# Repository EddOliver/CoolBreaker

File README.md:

# CoolBreaker: Automotive Smart Circuit breaker, and switch

https://www.hackster.io/Edoliver/coolbreaker-automotive-smart-circuit-breaker-and-switch-d4b7d0

## Automotive Smart Circuit breaker and switch to increase efficiency in your car's electrical system and prevent electrical hazards.

## Bill of Materials

Hardware components
- CoolMOS C7 Gold SJ MOSFET	
- Infineon CoolMOS C7 Gold SJ MOSFET×	1	
- Custom PCB	
- Adafruit Feather HUZZAH with ESP32×	1	
- Infineon EiceDriver	x1	
- Capacitor 100 nF	
- Capacitor 10 µF
- 10R Resistor
- 3R3 Resistor	
- DFRobot ACS758 Current Sensor board

Software apps and online services
- Autodesk Eagle
- Fusion 360	
- Autodesk Fusion 360

## Story
CoolBreaker: Automotive Smart Circuit breaker, battery protection and switch.

## Introduction and problem
For several years now the automotive industry have relied on car fuses as they are cheap and easily changeable. Most cars have a fuse box that looks like this in order to manage their electrical system:

Even Teslas use a fuse box when dealing with Accesory wiring and internal electrical systems:

https://www.carcarekiosk.com/video/2017_Tesla_S_90D_Electric/fuse_interior/replace

Ordinary car fuses generally used in most applications have several drawbacks and they can be inefficient in case of a short circuit or with faulty electrical systems. If you don't believe me, let's ask motoforlife:

https://www.youtube.com/watch?v=sIqoVgxmnvQ

Nowadays we have cars with a lot of accesories. Lights, USB ports that in turn power more devices, audio systems, even refrigerators in some trucks and more. And we want even more stuff.

But, what do we have in hand for electrical automotive protection?

1.- More Fuses (with all their drawbacks).

2.- Mechanical and electromechanical Circuit breakers.

3.- Relay harnesses.

Lets analyze both options:

### Fuses and Relays

Relays are everywhere in a car, and they are seldom solid state ones.

Well, fuses are just like the ones we used to have at homes or in home appliances. As a current above their limit passes through the wire, it melts it breaking it and thus the circuit. There's a huge reason we have already moved on from those in relation to home use as they are unreliable and almost dangerous in some aspects. Yes, the automotive industry uses them because they are cheap and easily changeable, but in order to find a fault you have to go in with a multimeter still and find it by hand like in the following video:

https://www.youtube.com/watch?v=n5FJDgcdii8

As you can see these kind of systems do little to automatically find problems related to batteries dying, and the most expensive part of the electrical system is, you guessed it, the battery. And they can be faulty with time, as shown in the video.

The second alternative is a circuitbreaker, but in automotive terms what you can get is one of these:
https://www.youtube.com/watch?v=vA1cz021OvU

That is just using again the thermal properties of the metal inside to break the circuit. They are also prone to failing and if there's rattling or movement they are unreliable.

Until very recently there were few alternatives to electromechanical and magnetic circuit breakers. They have undesirable characteristics such as arcing and switch bounce (with corresponding noise and wear), while accomodating large unwieldly packages in their high power systems.

Racing and rally cars are already moving on from these kind of solutions as they both expect heavy usage, rattling, noise, and sometimes they need to kill the battery (because of fires and explosions) so they use solid state solutions for those, even remote ones.

Even aircraft has improved their capabilities with solid state solutions such as: http://verticalpower.com

There is no other option easily attainable in the market nowadays....let's try building one.

## Solution
Enter CoolBreaker the Solid State Circuit Breaker using the extremely impressive CoolMOS 600 C7 from Infineon.

If you are going to replicate this experiment please use every security measure possible, DC energy is much safer that AC but still when managing these currents accidents can happen.

Solid state technology applied to this traditional device has resulted in circuit breakers free from arcing and switch bounce, that offer correspondingly higher reliability and longer lifetimes as well as faster switching times. A typical solid state circuit breaker will switch in a matter of microseconds, as opposed to milliseconds or even seconds for a mechanical version. New solid state products currently on the market utilize the many benefits associated with power MOSFETs to deliver aproduct far superior to earlier silicon versions. PowerMOSFETs offer low on resistances (as compared to bipolar transistors), low voltage drops, low EMI, faster switching times and good thermal stability of key parameters. And we have the latest technology in the CoolMOS C7 provided by infineon.

Now to the fun part.

What do we want in the product?

For it to be reliable, the switching times of the CoolMOS provides us that.
Cheap in comparison with fuses and mechanical circuit breakers and Relays. If we use a MOSFET driver and the CoolMOS we can achieve that with a simple circuit.
We might want to know of any parasitic currents that are draining the battery. Hall efect sensor? Yeah let's go with a Hall effect sensor.
For it to be smart. We want to know exactly which accesory is short circuiting. You saw this coming in the era of IoT. This will increase the base price but for this prototype, it'll be fun.
It has to be small enough (taking into consideration that we can just build a PCB instead of a panel this will be easy to achieve).
A solid state solution for this will actually be leaps and bounds better than the previous ones as it'll be imprevious to water, weather, grime, oxidation, tough environments, rattling and all the problems that we find in fuses and electromechanical solutions.

We have to take into consideration that this will be an auxiliary to the PDU for the accesories. Powering up a vehicle requires between 250 and 1000 amps for a cold start so it is quite difficult to do just with silicon. This product will be able to protect your accesories, your battery and will increment its electrical efficiency enourmously.

## Design
Instead of fitting everything into a small pcb and lets say controlling everything via an ATTiny, I want this proyect to be easily doable for any maker at home without having to order expensive PCB that he may not be able to solder, so everything will be done in a modular fashion.

We will be using:

A hall effect sensor module based on the ACS758 which is a very reliable and robust sensor.

The Infineon EiceDRIVER to set the logic and protect the Microcontroller.

And we will control it via the Adafruit's Feather HUZZAH with the ESP32 in order to get info into our cellphone and perhaps even reset capabilities. (notice that logic is 3.3V!)

To use the CoolMOS we indeed will build a little pcb module.
I want to know two things with this setup, exactly how much current is passing through and if it passes our threshold that will be determined by the load. This will be done on an app and via serial obviously.

## First step:
First I began designing the PCB as the CoolMOS provided by Infineon came in, is SMD version on a HSOF package.

The main goal for this module is to create a PCB that can be attached via headers to any other contraption that the community might want to design later. YES, the module by itself is marketable as it provides an easy way for makers and hobbyists to come up with new solutions.

This is a community of makers in the end so a module with the CoolMOS and its Driver was the way to go.

The proper driver for the CoolMOS is the 1EDI60N12AF EiceDRIVER by Infineon. In order to create the module first I went to its Datasheet and according to its characteristics I decided on following up with this design, you have to choose the resistors according to your application(see this application note:https://www.infineon.com/dgdl/Infineon-EiceDRIVER-Gate+resistor+for+power+devices-AN-v01_00-EN.pdf?fileId=5546d462518ffd8501523ee694b74f18), for mine this one sufficed.:

Then checking the CoolMOS' datasheet I found that it has a special pin for the driver. Very Interesting.

Then according to the guide of use in the official site of the driver I followed through and designed the following schematic:

As you can see the intention is to use pinheaders on one side for the logic part and Screw terminals for the power side. With this we separate power from logic and protect our microcontrollers accordingly (And those expensive Bluetooth boards!). Number 1 on the screw terminals goes to the load, that in this case will be a Halogen lamp but can be whatever.

Here is a picture of the Gerber files before being sent to be made:

As you can see I went for big clearance and width as it is a power application, and to prevent any problem during manufacturing.

After a while they arrived!

And the soldering process began. It was arduous but relaxing as I forgot to buy solder paste, nevertheless you can see the process in the build video.

Here is the result:

## Second step
Now its time to go full circle and create the full product by joining the boards together. But first, time to test everything in the lab!

Here is the building process with a little narration:

https://www.youtube.com/watch?v=XJemC6Y_ZpY

Here is the schematic of the modules joined together:

As you can see we have the Adafruit Huzzah ESP32 for the logic and to switch the MOSFET via its driver. Tied to that we have the hall sensor to detect when the Current passes the threshold and break the circuit by swithching the MOSFET.

To know the current we have to set the Hall sensor to the Feather logic.

I know what you are saying: Ohhh but Edoliver the Feather ESP32 works on 3.3V logic!

Yeah I know, for that I set up a voltage divider with these characteristics:

Just grab Vin from the USB supply pin and from the middle grab that A0.

Now we have to make a Blynk app and upload the Code to the Feather HUZZAH (Code at the end). Blynk allow us to develop very fast IoT applications, remember when using the widgets to select the proper pins that you want to track. For every new app that you make in Blynk you should get an authentication number. You just have to download the app, set an account and you are set as there are countless examples of Arduino IDE sketches.

The intention of the app is to have reset capabilities at all times or shutdown the load whenever we need to.

At the same time whenever the current passes the threshold we setup in the code it switches the MOSFET to off.

readings[index1] = analogRead(A0); //Raw data reading
   readings[index1] = (readings[index1]-2048)*3.3/4096/0.04+5.04;//Data processing:510-raw data from analogRead when the input is 0; 5-5v; the first 0.04-0.04V/A(sensitivity); the second 0.04-offset val;
   total= total + readings[index1];       
   index1 = index1 + 1;                    
   if (index1 >= numReadings)              
     index1= 0;                           
   average = total/numReadings;   //Smoothing algorithm (http://www.arduino.cc/en/Tutorial/Smoothing)    
   currentValue= average;
   Serial.println(currentValue);
   if (currentValue > 5) digitalWrite(LED_BUILTIN, LOW);

This is the most important part of the code as you can see it reads the Analog pin A0 and sets a value for the current, if that value is bigger than the set threshold that in this case is 5 amps then the MOSFET is turned off.

I know what you are saying: Ohhh but Edoliver the Feather ESP32 works on 3.3V logic!

## Third and last step.
Testing and Showcase!

https://www.youtube.com/watch?v=gUYDCipCUN8

## Future Rollout and Analysis
So we have a tentative module for 13 Dollar aproximatelly.

It protects from overcurrents
It stops the battery from draining if there are still parasitic currents.
It is smart as it can be controlled from your phone.
It is solid state so any rattling or mechanical parts will not prevent it from functioning correctly.
Provides quicker intervention time, less maintenance, less footprint and more safety.
If we compare it with:

https://www.amazon.com/Tocas-Manual-Profile-Circuit-Breakers/dp/B073S46K4M/ref=sr_1_3?ie=UTF8&qid=1547813899&sr=8-3&keywords=automotive%2Bcircuit%2Bbreaker&th=1

These are only fuses and are much more expensive.

And Relay harnesses are about the same but with the known problems:

https://www.amazon.com/Nilight-Wiring-Harness-Waterproof-Warranty/dp/B073TYH2VN/ref=sr_1_6?ie=UTF8&qid=1548483118&sr=8-6&keywords=relay+harness+elite

Adding the Bluetooth functionalities the prize increases by 5 dollars but there is nothing in the market quite like it. And if we compare it to some of the best circuit breakers in the market the prize is very competitive.

- For the future rollout, I might expand to control the current at which the circuit will break via bluetooth in order to fit every car accessory.

Thank you for reading along!

References:
Took huge inspiration from Electroboom and Great Scott's youtube channels:

https://www.youtube.com/user/msadaghd

https://www.youtube.com/user/greatscottlab

Circuit heavily based on the following paper:

https://www.eeweb.com/app-notes/solid-state-circuit-breaker

If you want to go deep into the rabbit hole of automotive electrical systems:

https://www.reddit.com/r/askscience/comments/lfwj7/why_do_cars_have_fuses_and_not_breakers/

https://news.ycombinator.com/item?id=8869221

https://www.e46fanatics.com/forum/showthread.php?t=627979

https://www.quora.com/Why-do-cars-uses-fuses-rather-than-circuit-breakers

https://www.consumerreports.org/hybrids-evs/electric-cars-101-the-answers-to-all-your-ev-questions/

https://www.infineon.com/dgdl/Infineon-EiceDRIVER-Gate+resistor+for+power+devices-AN-v01_00-EN.pdf?fileId=5546d462518ffd8501523ee694b74f18

https://www.infineon.com/dgdl/Infineon-IPT60R028G7-DS-v02_00-EN.pdf?fileId=5546d46259d9a4bf015a13e82df70e30

https://www.infineon.com/cms/en/product/power/gate-driver-ics/1edi60n12af/?intc=reco#

https://www.infineon.com/dgdl/Infineon-1EDI60N12AF-DS-v02_00-EN.pdf?fileId=db3a3043427ac3e201428e5da08f372a

https://learn.adafruit.com/adafruit-huzzah32-esp32-feather/pinouts

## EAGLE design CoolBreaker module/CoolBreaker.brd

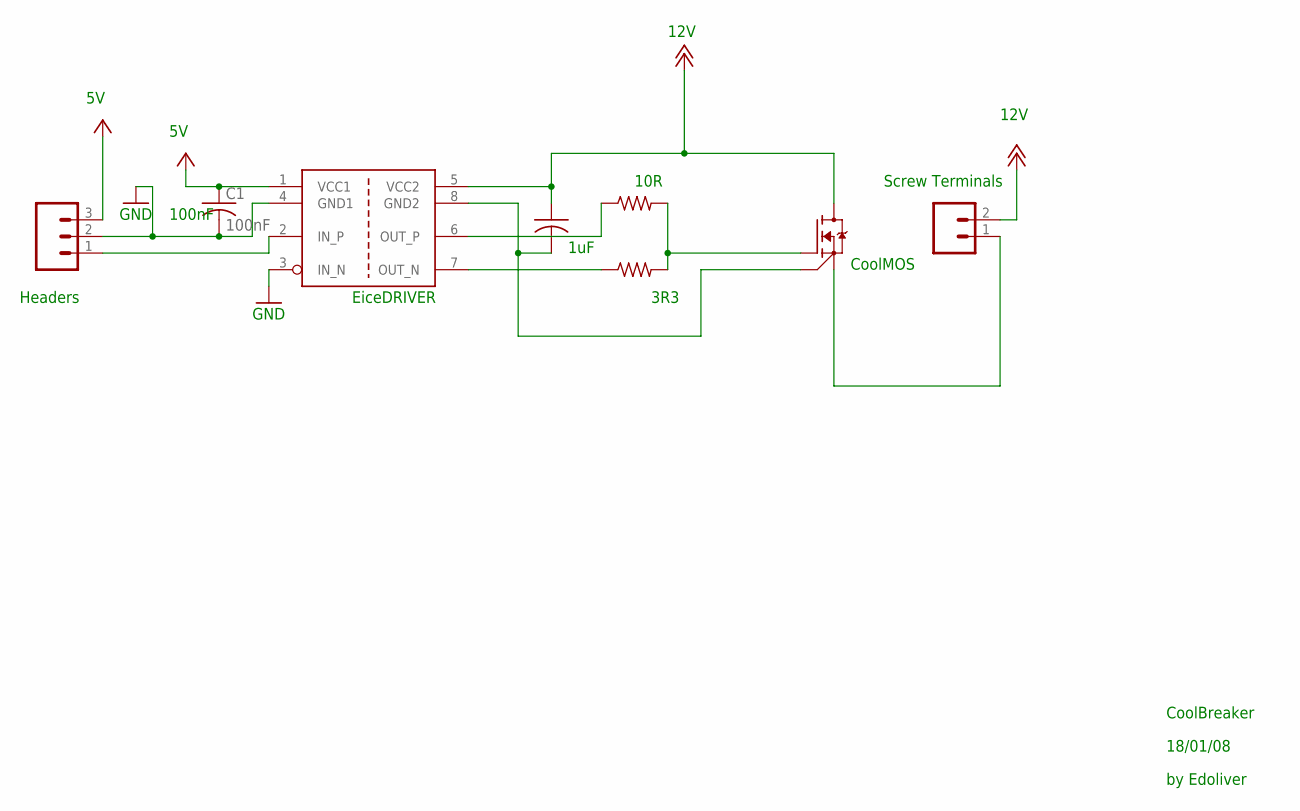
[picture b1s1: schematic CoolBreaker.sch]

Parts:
C1: 100nF; C025-024X044
C2: 1uF; C025-024X044
J1: CONN_025MM; SCREWTERMINAL-5MM-2
J2: 455-1750-1-ND; 1X03
Q1: IPT65R033G7XTMA1; TRANS_IPT65R033G7XTMA1
R1: 3R3; 0204/7
R2: 10R; 0204/7
U1: 1EDI60N12AF; SOIC127P600X175-8N-10

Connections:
+5V: C1.1, J2.3, U1.1 (VCC1)
+12V: C2.1, J1.2, Q1.9 (DRAIN), U1.5 (VCC2)
GND: C1.2, J2.2, U1.3 (IN_N), U1.4 (GND1)
unnamed: C2.2, Q1.2 (DRIVER_SOURCE), U1.8 (GND2)
unnamed: R2.1, U1.6 (OUT_P)
unnamed: R1.1, U1.7 (OUT_N)
unnamed: Q1.1 (GATE), R1.2, R2.2
unnamed: J2.1, U1.2 (IN_P)
unnamed: J1.1, Q1.3 (SOURCE), Q1.4 (SOURCE), Q1.5 (SOURCE), Q1.6 (SOURCE), Q1.7 (SOURCE), Q1.8 (SOURCE)

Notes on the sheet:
Headers
GND
100nF
1uF
10R
3R3
12V
CoolMOS
Screw Terminals
EiceDRIVER
CoolBreaker
18/01/08
by Edoliver

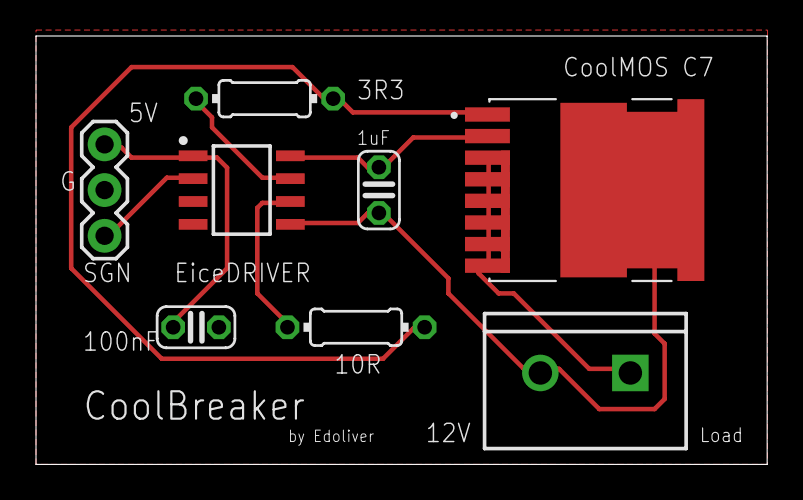
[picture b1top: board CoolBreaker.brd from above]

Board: 2 copper layers, 40.6 x 23.8 mm, 8 parts (0 on the bottom side), 9 nets.

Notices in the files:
parts and their libraries:
SparkFun-Connectors: Licensing: Creative Commons ShareAlike 4.0 International - https://creativecommons.org/licenses/by-sa/4.0
